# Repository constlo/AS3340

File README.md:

# AS3340
A custom-made PCB for the AS3340 IC

AS3340 is a voltage-controlled oscillator. This board is made with the specs specified in the datasheet of the AS3340, which can be found [here](https://www.alfarzpp.lv/eng/sc/AS3340.pdf).

I also included a 555-based negative voltage generator for this circuit, as the board specifies a need for it. Vcc is rated at 15V, and Vee is approximately -13V.

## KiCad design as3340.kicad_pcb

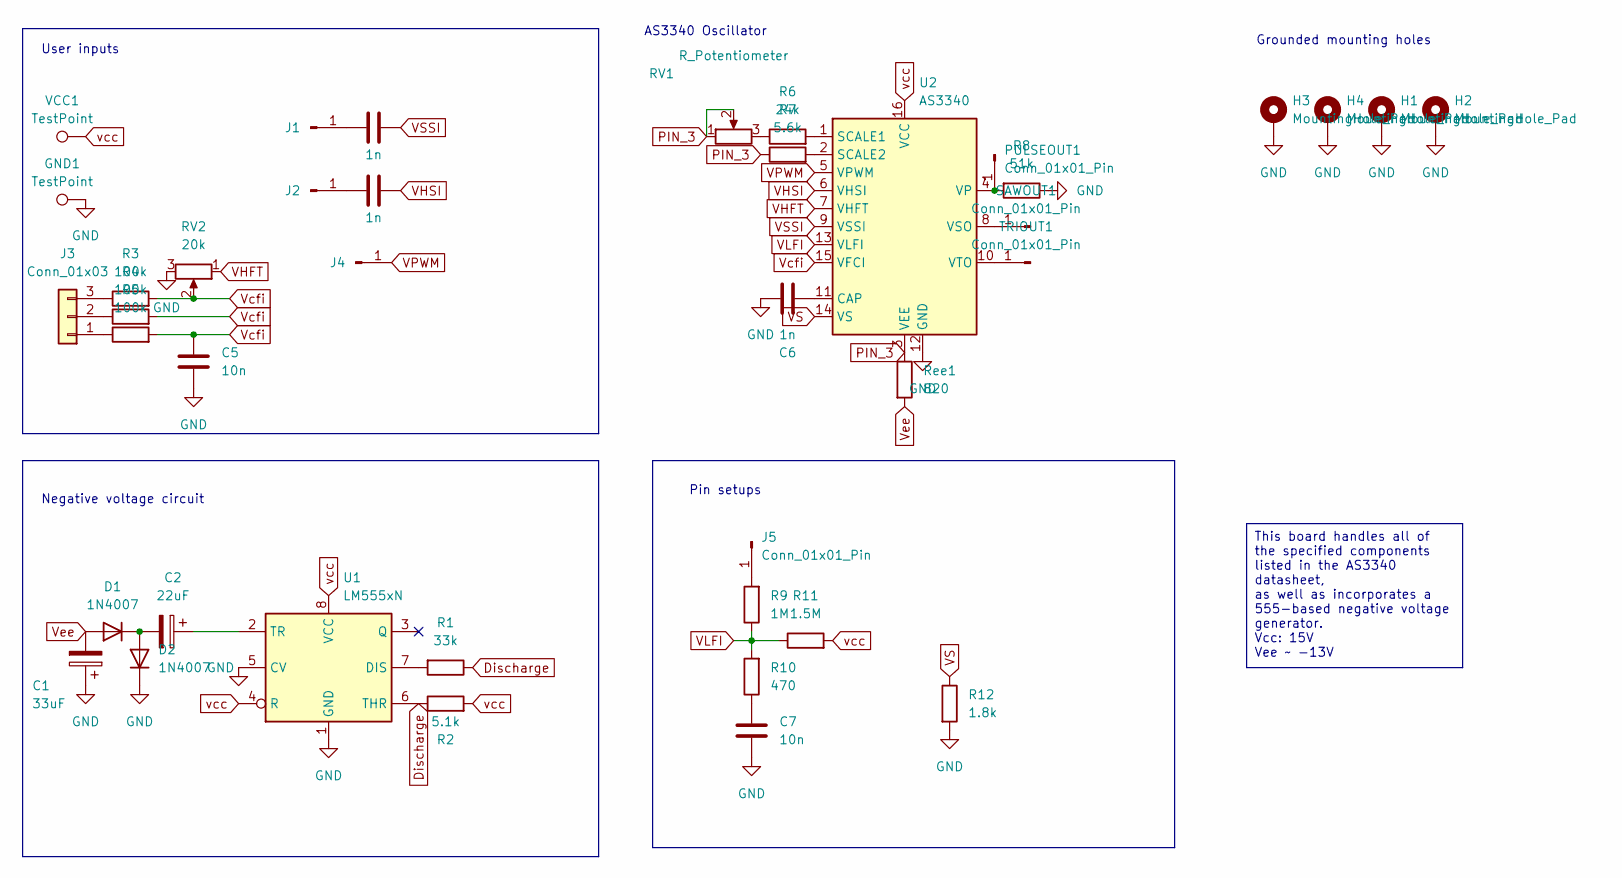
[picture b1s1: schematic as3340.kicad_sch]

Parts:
C1: 33uF; CP_Radial_D6.3mm_P2.50mm
C2: 22uF; CP_Radial_D6.3mm_P2.50mm
C3, C4, C6: 1n; C_1206_3216Metric_Pad1.33x1.80mm_HandSolder
C5, C7: 10n; C_1206_3216Metric_Pad1.33x1.80mm_HandSolder
D1, D2: 1N4007; D_DO-41_SOD81_P7.62mm_Horizontal
GND1: TestPoint; TestPoint_Pad_D2.0mm
H1, H2, H3, H4: MountingHole_Pad; MountingHole_3.2mm_M3_Pad
J1, J2, J4, J5: Conn_01x01_Pin; PinSocket_1x01_P2.54mm_Vertical
J3: Conn_01x03; PinSocket_1x03_P2.54mm_Vertical
PULSEOUT1: Conn_01x01_Pin; PinSocket_1x01_P2.54mm_Vertical
R1: 33k; R_1206_3216Metric_Pad1.30x1.75mm_HandSolder
R2: 5.1k; R_1206_3216Metric_Pad1.30x1.75mm_HandSolder
R3, R4, R5: 100k; R_1206_3216Metric_Pad1.30x1.75mm_HandSolder
R6: 24k; R_1206_3216Metric_Pad1.30x1.75mm_HandSolder
R7: 5.6k; R_1206_3216Metric_Pad1.30x1.75mm_HandSolder
R8: 51k; R_1206_3216Metric_Pad1.30x1.75mm_HandSolder
R9: 1M; R_1206_3216Metric_Pad1.30x1.75mm_HandSolder
R10: 470; R_1206_3216Metric_Pad1.30x1.75mm_HandSolder
R11: 1.5M; R_1206_3216Metric_Pad1.30x1.75mm_HandSolder
R12: 1.8k; R_1206_3216Metric_Pad1.30x1.75mm_HandSolder
RV1: R_Potentiometer; Potentiometer_ACP_CA6-VSMD_Vertical
RV2: 20k; Potentiometer_ACP_CA6-VSMD_Vertical
Ree1: 820; R_1206_3216Metric_Pad1.30x1.75mm_HandSolder
SAWOUT1: Conn_01x01_Pin; PinSocket_1x01_P2.54mm_Vertical
TRIOUT1: Conn_01x01_Pin; PinSocket_1x01_P2.54mm_Vertical
U1: LM555xN; DIP-8_W7.62mm
U2: AS3340; DIP-16_W7.62mm_LongPads
VCC1: TestPoint; TestPoint_Pad_D2.0mm

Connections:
Discharge: R1.1, R2.1, U1.6 (THR)
GND: C1.1, C5.1, C6.1, C7.1, D2.1 (K), GND1.1, H1.1, H2.1, H3.1, H4.1, R8.1, R12.2, RV2.3, U1.1 (GND), U1.5 (CV), U2.12 (GND)
unnamed: C7.2, R10.1
unnamed: C2.2, D1.1 (K), D2.2 (A)
unnamed: C3.1, J1.1
unnamed: C4.1, J2.1
unnamed: J3.1, R5.1
unnamed: J3.2, R4.1
unnamed: J3.3, R3.1
unnamed: J5.1, R9.2
unnamed: PULSEOUT1.1, R8.2, U2.4 (VP)
unnamed: R6.1, RV1.3
unnamed: SAWOUT1.1, U2.8 (VSO)
unnamed: TRIOUT1.1, U2.10 (VTO)
unnamed: R1.2, U1.7 (DIS)
unnamed: C2.1, U1.2 (TR)
unnamed: C6.2, U2.11 (CAP)
unnamed: R6.2, U2.1 (SCALE1)
unnamed: R7.2, U2.2 (SCALE2)
PIN_3: R7.1, RV1.1, RV1.2, Ree1.1, U2.3 (VEE)
VHFT: RV2.1, U2.7 (VHFT)
VHSI: C4.2, U2.6 (VHSI)
VLFI: R9.1, R10.2, R11.1, U2.13 (VLFI)
VPWM: J4.1, U2.5 (VPWM)
VS: R12.1, U2.14 (VS)
VSSI: C3.2, U2.9 (VSSI)
Vcfi: C5.2, R3.2, R4.2, R5.2, RV2.2, U2.15 (VFCI)
Vee: C1.2, D1.2 (A), Ree1.2
vcc: R2.2, R11.2, U1.4 (R), U1.8 (VCC), U2.16 (VCC), VCC1.1

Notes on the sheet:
This board handles all of the specified components listed in the AS3340 datasheet, as well as incorporates a 555-based negative voltage generator. Vcc: 15V Vee ~ -13V
AS3340 Oscillator
Negative voltage circuit
User inputs
Grounded mounting holes
Pin setups

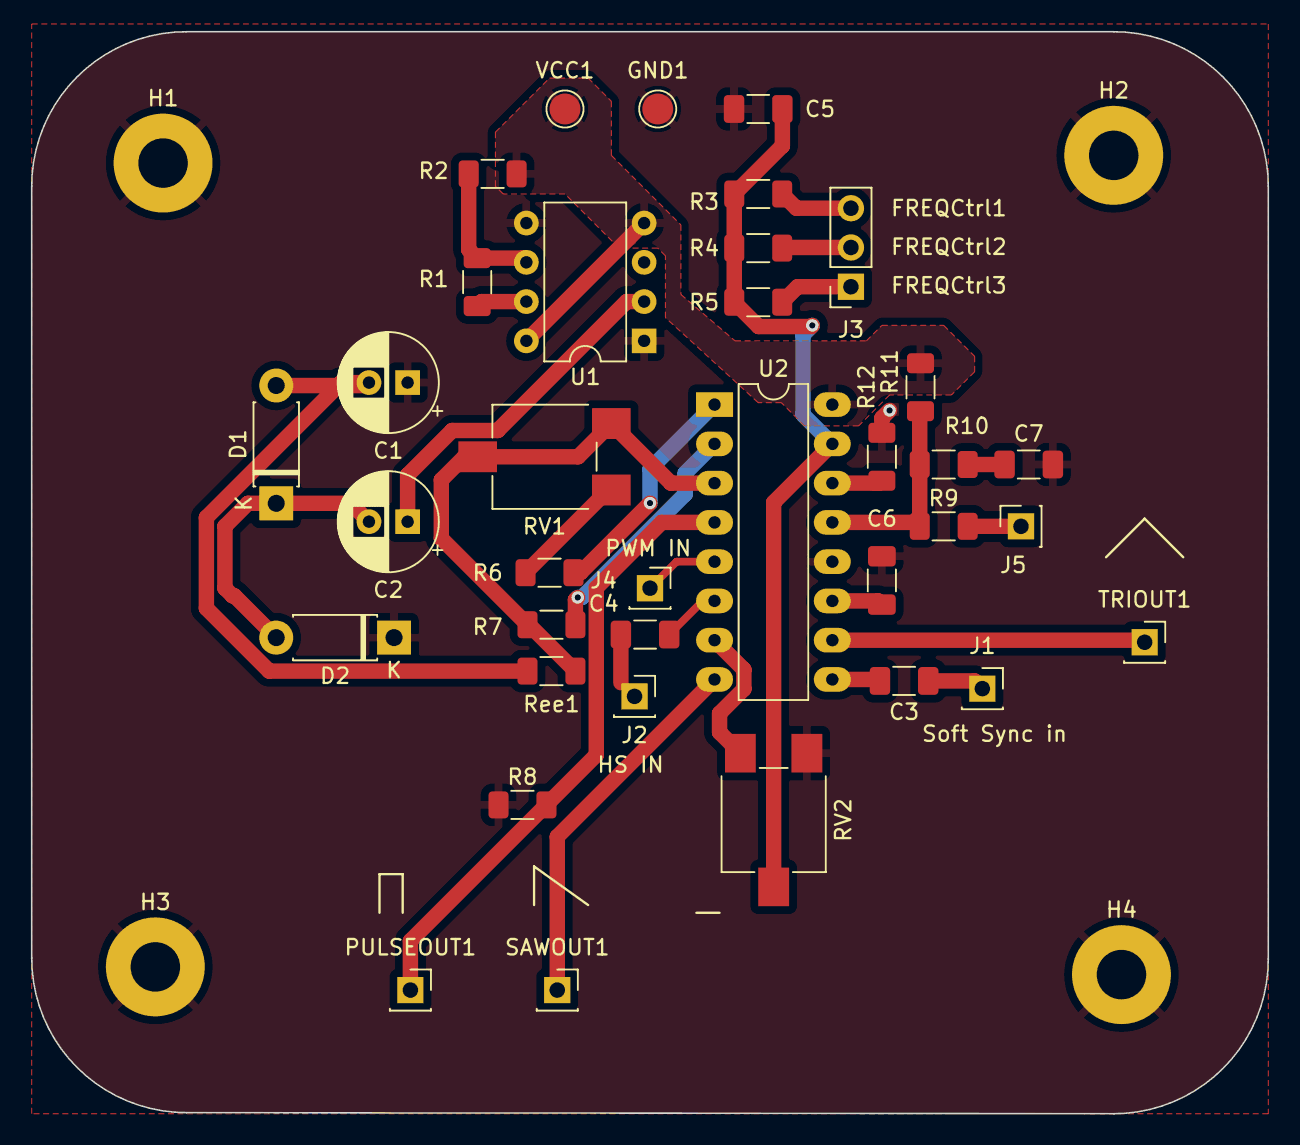
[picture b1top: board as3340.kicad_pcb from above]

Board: 2 copper layers, 80.0 x 70.0 mm, 40 parts (0 on the bottom side), 29 nets.

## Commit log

2023-08-06 added board
2023-08-06 Added iamges
